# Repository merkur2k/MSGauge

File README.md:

MegaSquirt CANbus gauge
==================

This is a simple single gauge for the [MegaSquirt](http://www.msextra.com/) Engine Controller.
It connects via CANbus and can output either via a 1.3" OLED display
or a small Switec X25 series stepper motor gauge needle driver.

It is built using the ARM [mbed](https://www.mbed.com/en/) platform, or more specicically a
port of it to GCC - [gcc4mbed](https://github.com/adamgreen/gcc4mbed/).

Quick start:
-----------
```
git clone https://github.com/merkur2k/MSGauge.git
cd MSGauge
git clone https://github.com/adamgreen/gcc4mbed.git
```
Follow the instructions at https://github.com/adamgreen/gcc4mbed/ to build gcc4mbed for your platform.
Build one of the gauge types:
```
cd MSGauge_OLED
make
```
or
```
cd MSGauge_Stepper
make
```
Use an ISP utility such as flash Magic (Windows) or lpc21isp (Linux) to flash the .bin or .hex in the LPC11C24 folder.

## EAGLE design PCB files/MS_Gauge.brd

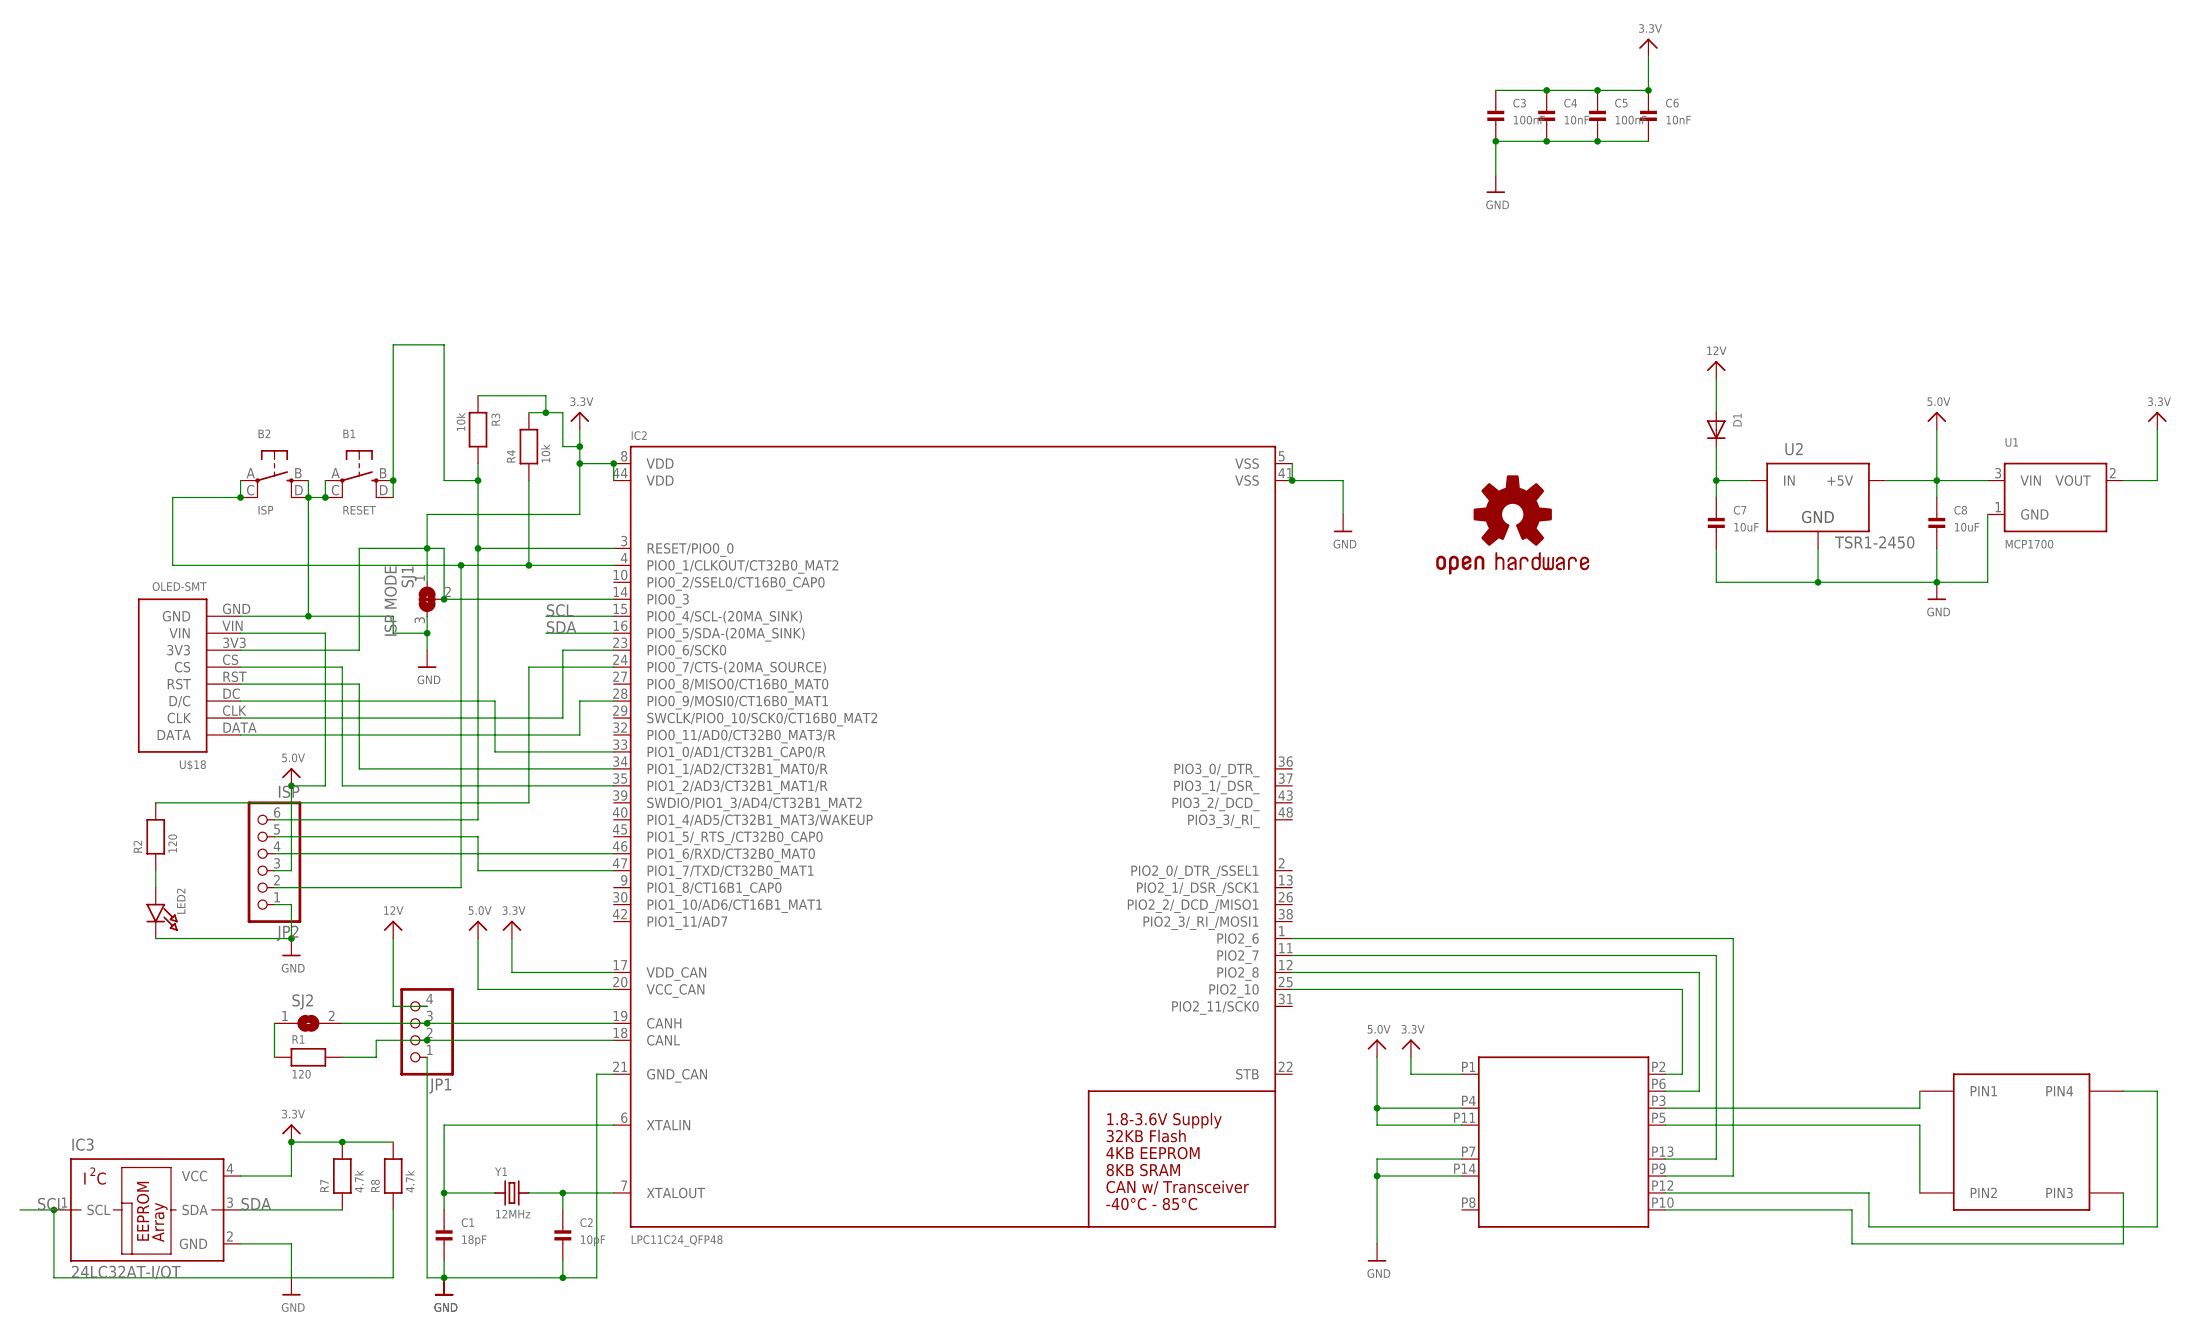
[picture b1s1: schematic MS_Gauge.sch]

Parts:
B1: RESET; BTN_EVQPQ_4.5MM
B2: ISP; BTN_EVQPQ_4.5MM
C1: 18pF; 0603
C2: 10pF; 0603
C3, C5: 100nF; 0603
C4, C6: 10nF; 0603
C7, C8: 10uF; 1206
D1: DIODESMA; SMADIODE
IC1: B1836M; MFP14S
IC2: LPC11C24_QFP48; LQFP48
IC3: 24LC32AT-I/OT; SOT23-5L
JP1: HEADER-1X4ROUND; 1X04_ROUND
JP2: ISP; 1X06_SMT
LED2: LED0603; CHIPLED_0603
LOGO1: OSHW-LOGOL; OSHW-LOGO-L
R1, R2: 120; 0603
R3, R4: 10k; 0603
R7, R8: 4.7k; 0603
SJ1: ISP MODE; SOLDERJUMPER_2WAY_OPEN_0805
SJ2: SOLDERJUMPER; SOLDERJUMPER_ARROW_NOPASTE
U1: MCP1700; SOT23-R
U2: TSR1-2450; TSR-1
U$1: VID29-FLIPPED
U$18: OLED-SMT; OLED-1.3-SMT
Y1: 12MHz; CRYSTAL_3.2X2.5

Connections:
3.3V: C3.1, C4.1, C5.1, C6.1, IC1.P1 (VCC), IC2.8 (VDD), IC2.14 (PIO0_3), IC2.17 (VDD_CAN), IC2.44 (VDD), IC3.4 (VCC), R3.1, R4.2, R7.2, R8.2, SJ1.1, SJ1.2, U1.2 (VOUT), U$18.3V3
5.0V: C8.1, IC1.P4 (VS1), IC1.P11 (VS2), IC2.20 (VCC_CAN), JP2.3, U1.3 (VIN), U2.3 (+5V), U$18.VIN
12V: D1.A, JP1.4
GND: B1.A, B1.C (P1), B2.B (S), B2.D (S1), C1.2, C2.2, C3.2, C4.2, C5.2, C6.2, C7.2, C8.2, IC1.P7 (GND1), IC1.P14 (GND2), IC2.5 (VSS), IC2.21 (GND_CAN), IC2.41 (VSS), IC3.2 (GND), JP1.1, JP2.1, LED2.C, SJ1.3, U1.1 (GND), U2.2 (GND), U$18.GND
unnamed: R1.1, SJ2.1
unnamed: IC2.18 (CANL), JP1.2, R1.2
unnamed: C2.1, IC2.7 (XTALOUT), Y1.2
unnamed: C1.1, IC2.6 (XTALIN), Y1.1
unnamed: B2.A, B2.C (P1), IC2.4 (PIO0_1/CLKOUT/CT32B0_MAT2), JP2.2, R4.1
unnamed: IC1.P2 (IN1), IC2.25 (PIO2_10)
unnamed: B1.B (S), B1.D (S1), IC2.3 (RESET/PIO0_0), JP2.6, R3.2
unnamed: IC1.P13 (IN3), IC2.11 (PIO2_7)
unnamed: IC1.P9 (IN4), IC2.1 (PIO2_6)
unnamed: IC1.P3 (OUT1), U$1.PIN1
unnamed: C7.1, D1.C, U2.1 (IN)
unnamed: IC1.P5 (OUT2), U$1.PIN2
unnamed: IC1.P12 (OUT3), U$1.PIN4
unnamed: IC1.P10 (OUT4), U$1.PIN3
unnamed: IC2.19 (CANH), JP1.3, SJ2.2
unnamed: IC2.46 (PIO1_6/RXD/CT32B0_MAT0), JP2.4
unnamed: IC2.47 (PIO1_7/TXD/CT32B0_MAT1), JP2.5
unnamed: IC2.28 (PIO0_9/MOSI0/CT16B0_MAT1), U$18.DATA
unnamed: IC2.33 (PIO1_0/AD1/CT32B1_CAP0/R), U$18.DC (D/C)
unnamed: IC2.34 (PIO1_1/AD2/CT32B1_MAT0/R), U$18.RST
unnamed: IC2.23 (PIO0_6/SCK0), U$18.CLK
unnamed: IC2.35 (PIO1_2/AD3/CT32B1_MAT1/R), U$18.CS
unnamed: IC2.24 (PIO0_7/CTS-(20MA_SOURCE)), R2.2
unnamed: LED2.A, R2.1
unnamed: IC1.P6 (IN2), IC2.12 (PIO2_8)
SCL: IC2.15 (PIO0_4/SCL-(20MA_SINK)), IC3.1 (SCL), R8.1
SDA: IC2.16 (PIO0_5/SDA-(20MA_SINK)), IC3.3 (SDA), R7.1

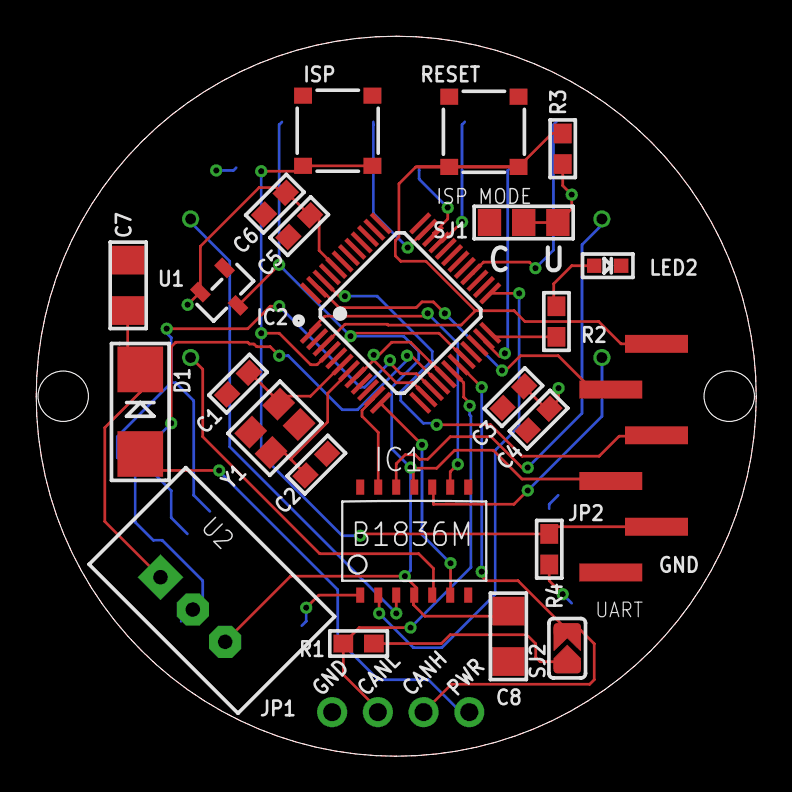
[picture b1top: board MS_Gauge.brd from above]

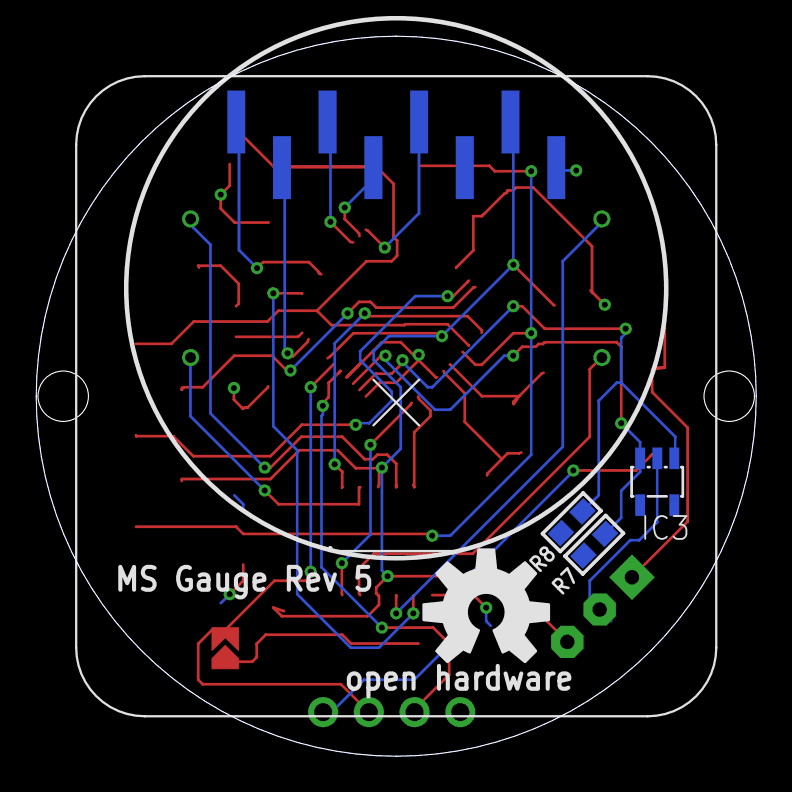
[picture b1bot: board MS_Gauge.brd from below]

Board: 2 copper layers, 40.0 x 40.0 mm, 31 parts (6 on the bottom side), 31 nets.

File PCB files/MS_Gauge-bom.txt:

Partlist exported from C:/Users/devnull/Documents/eagle/MS_Gauge/MS_Gauge.sch at 3/21/2015 4:39:10 PM

Part  Value          Device                Package                     Description                    
B1    ISP            SWITCH_TACT_SMTEVQPQ  BTN_EVQPQ_4.5MM             SMT Tact Switches                  http://www.mouser.com/ProductDetail/Panasonic/EVQ-PQHB55/?qs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
B2    ISP            SWITCH_TACT_SMTEVQPQ  BTN_EVQPQ_4.5MM             SMT Tact Switches                  http://www.mouser.com/ProductDetail/Panasonic/EVQ-PQHB55/?qs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
C1    18pF           CAP_CERAMIC0603       0603                        Ceramic Capacitors                 http://www.mouser.com/ProductDetail/AVX/06035A180GAT2A/?qs=s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
C2    10pF           CAP_CERAMIC0603       0603                        Ceramic Capacitors                 http://www.mouser.com/ProductDetail/AVX/06031C103KAT2A/?qs=s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
C3    100nF          CAP_CERAMIC0603       0603                        Ceramic Capacitors                 http://www.mouser.com/ProductDetail/AVX/06035C104KAT2A/?qs=s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
C4    10nF           CAP_CERAMIC0603       0603                        Ceramic Capacitors             
C5    100nF          CAP_CERAMIC0603       0603                        Ceramic Capacitors             
C6    10nF           CAP_CERAMIC0603       0603                        Ceramic Capacitors             
C7    10uF           CAP_CERAMIC1206       1206                        Ceramic Capacitors                 http://www.mouser.com/ProductDetail/Murata-Electronics/GCM31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
C8    10uF           CAP_CERAMIC1206       1206                        Ceramic Capacitors             
D1                   DIODESMA              SMADIODE                    Diode                              http://www.mouser.com/ProductDetail/STMicroelectronics/STTH1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
IC1   B1836M         B1836M                MFP14S            
IC2   LPC11C24_QFP48 LPC11C24_QFP48        LQFP48                                                         http://www.mouser.com/ProductDetail/NXP-Semiconductors/LPC11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
IC3   24LC32AT-I/OT  24LC32AT-I/OT         SOT23-5L  
JP1                  HEADER-1X4ROUND       1X04_ROUND                  PIN HEADER                     
JP2   ISP            HEADER-1X6SMT         1X06_SMT                    PIN HEADER                         http://www.mouser.com/ProductDetail/Molex/87898-0626/?qs=sGA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
LED2                 LED0603               CHIPLED_0603                LED     
R1    120            RESISTOR0603          0603                        Resistors                          http://www.mouser.com/ProductDetail/Panasonic/ERJ-3GEYJ121V/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
R2    120            RESISTOR0603          0603                        Resistors                        
R3    10k            RESISTOR0603          0603                        Resistors                        
R4    10k            RESISTOR0603          0603                        Resistors                        
R7    4.7k           RESISTOR0603          0603                        Resistors                        
R8    4.7k           RESISTOR0603          0603                        Resistors  
U$1   VID29-FLIPPED  VID29-FLIPPED         VID29-FLIPPED                                              
U$18  OLED-SMT       OLED-SMT              OLED-1.3-SMT                                                   http://www.mouser.com/ProductDetail/Molex/87898-0426/?qs=sGA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
U1                   VREG_SOT23            SOT23-R                     SOT23 Fixed Voltage Regulators     http://www.mouser.com/ProductDetail/Microchip-Technology/MCP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
U2    TSR1-2450      TSR1-2450             TSR-1                       Traco Power TSR 1-2450             http://www.mouser.com/ProductDetail/RECOM-Power/R-78E50-05/?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 
Y1    12MHz          CRYSTALTHIN           CRYSTAL_3.2X2.5             Crystals                           http://www.mouser.com/ProductDetail/ABRACON/ABM8G-12000MHZ-B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

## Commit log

2015-10-13 Move things around to prepare for two source trees
2015-10-13 Add stepper motor version
2015-10-13 Further reorginization and initial commit of stepper version
2015-10-13 Adding Stepper gauge code
2015-10-13 Add PCB artwork Eagle files
2015-10-19 Update Eagle files to Rev 4. Fixes wrong reset button wiring, adds termination resistor solder jumper.
2015-10-19 Update Eagle files to Rev 5. Adds i2c eeprom.
2015-10-24 Minor routing changes to PCB
2015-10-24 Add basic BOM
2015-10-26 BOM updates

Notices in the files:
parts and their libraries:
microbuilder: This work is placed in the public domain, and may be freely used for commercial and non-commercial work with the following conditions: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
SparkFun-Aesthetics: Licensing: Creative Commons ShareAlike 4.0 International - https://creativecommons.org/licenses/by-sa/4.0
